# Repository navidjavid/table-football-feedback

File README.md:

# Table Football Feedback System ⚽

A smart foosball table built for the UbiLab university course. The table
identifies players by RFID, tracks the ball and score in real time, shows
match status on an on-cabinet LCD per side, and streams everything live
to a web dashboard hosted on a Raspberry Pi 4 — no internet connection
required, the Pi runs its own WiFi hotspot.

This repo contains **two independently-runnable projects**:

| Part | Where | Runs on | Language |
|---|---|---|---|
| Embedded firmware | `src/`, `include/`, `lib/` | Raspberry Pi Pico 2 W ×2 | C (Pico SDK) |
| Server + dashboard | `server/` | Raspberry Pi 4 | Python (Flask) |

They talk to each other over MQTT/WiFi — but the two Picos also talk
**directly to each other** over a shared I2C bus, so registration keeps
working even with no Pi/WiFi present at all (see §3).

---

## 1. System overview

```
 ┌──────────────┐                 ┌──────────────────────┐   ┌──────────────────────┐
 │ Ball tracker │────I2C (shared)▶│  Side A PCB           │   │  Side B PCB           │
 │ (external,   │────────────────▶│  Pico 2W + RFID +     │◀─▶│  Pico 2W + RFID +     │
 │  other team) │  both boards    │  display (PRIMARY)    │I2C│  display (SECONDARY)  │
 └──────────────┘  listen         └───────────┬──────────┘   └──────────┬────────────┘
                                               │ MQTT/WiFi                │ MQTT/WiFi
                                               ▼                          ▼
                                   ┌─────────────────────────────────────────────┐
                                   │              Raspberry Pi 4                  │
                                   │  WiFi hotspot "TableFootball"                │
                                   │  Mosquitto MQTT broker                       │
                                   │  Flask web app (SSE) + SQLite (WAL)          │
                                   └───────────────────┬───────────────────────────┘
                                                       │ HTTP / SSE
                                                       ▼
                                           Any phone/laptop on the hotspot —
                                           live dashboard, player profiles,
                                           admin panel, tournament brackets
```

**Two independent PCBs, one per side** — each has its own Pico 2 W, PN532
RFID reader, and EA DOGL128 display. Both boards listen to the same
shared I2C bus from the ball-tracker hardware. Exactly one board is
configured `PICO_ROLE_PRIMARY` (owns reporting ball position/score/state
to the Pi); the other only reports its own side's RFID taps + heartbeat —
this avoids the server ever getting duplicate/racing data from both
boards for the same table.

**Data flow, end to end:**

1. A player taps an RFID card on either side's own PN532 reader.
2. That board reads the UID over SPI, registers it locally (own side's
   roster, up to 2 players for 2v2), and:
   - broadcasts it directly to the **sibling board** over the shared I2C
     bus (a board briefly becomes I2C master to send this — see §3),
     so the other side learns about it **with no Pi/WiFi involved**;
   - publishes it to the Pi over MQTT, which is authoritative for
     identity/history — it resolves the UID against its own SQLite
     database (or creates a guest), decides when the match should
     start, and echoes the resolved name back.
3. The primary board republishes ball x/y/speed/score at ~12 Hz from the
   shared I2C feed; the dashboard renders this as a moving dot on a mini
   pitch.
4. Goals are detected locally (baseline-diffed against the ball
   tracker's own score fields, not trusted directly) on **both** boards
   independently, each updating its own display; the primary board's
   published state drives the dashboard's "GOAL!" animation.
5. At game end, the Pi saves the full match (mode, score, players,
   fastest shot, winner) to SQLite — shows up in player profiles, match
   history, and tournament brackets.
6. If a table gets stuck in `GAME_PLAYING` with no update for 45s (a
   board crashed/rebooted mid-match), the Pi's own watchdog auto-abandons
   it — so a later reconnect never resumes a long-dead game.

`[PICTURE: photo of the assembled table — both enclosures, PN532s, LCDs visible]`

---

## 2. Physical components & wiring

### Hardware list (×2, one set per side)

- **Raspberry Pi Pico 2 W** — WiFi, RFID, display, local game logic
- **PN532 NFC/RFID reader module**, configured in **SPI mode** (DIP
  switches: SEL0=OFF, SEL1=ON)
- **EA DOGL128L-6** graphic LCD, 128×64, reflective (no backlight),
  driven with **bit-banged SPI** (hardware SPI caused timing issues on
  this clone)
- A custom 3D-printed enclosure (front panel + back shell,
  `hardware/enclosure/` in a sibling directory to this repo — not
  version-controlled here) with a display window and a cable
  pass-through for the shared I2C bus
- RFID cards, one per player — UID is the player's identity end to end

Plus shared infrastructure:
- An external **ball-tracker** (built by another team) that writes ball
  position packets over I2C to both boards
- **Raspberry Pi 4** (any RAM tier) + microSD (16 GB+) + 5V/3A USB-C
  power supply — runs the WiFi hotspot, MQTT broker, and Flask server

`[PICTURE: each component individually — Pico board, PN532 module with DIP switches labeled, EA DOGL128 display, an assembled enclosure, an RFID card]`

### Real-world table dimensions

The physical table is **140 cm long × 76 cm wide**. The dashboard's
field visualization is intentionally drawn at this exact 140:76 aspect
ratio (`server/static/style.css`, `.field { aspect-ratio: 140 / 76; }`),
and ball coordinates are normalized to a 0–1000 × 0–500 grid before
being sent over MQTT so the same ratio holds end to end.

`[PICTURE: top-down schematic of the table with dimensions labeled, goal positions marked]`

### Pin connections — per side board

| Component | Signal | Pico GPIO | Physical pin |
|---|---|---|---|
| PN532 (SPI1) | SCK | GP10 | 14 |
| | MOSI | GP11 | 15 |
| | MISO | GP12 | 16 |
| | NSS/CS | GP13 | 17 |
| | RSTO | GP15 | 20 |
| | VCC / GND | 3.3V / GND | 36 / 38 |
| EA DOGL128 (bit-bang SPI) | SI (MOSI) | GP19 | 25 |
| | SCL (SCK) | GP18 | 24 |
| | A0 (data/cmd) | GP20 | 26 |
| | RST | GP21 | 27 |
| | CS1B | GP17 | 22 |
| Shared ball-tracker I2C bus | SDA | GP4 | 6 |
| | SCL | GP5 | 7 |

The display additionally needs **9 capacitors** for its internal charge
pump (5×1µF on V0–V4, 3×1µF on the CAP1/2/3 chain, 4.7µF on VOUT) — see
[`docs/hardware_connections.md`](docs/hardware_connections.md) for the
full, datasheet-verified capacitor wiring table; it will not power on
without them, and the topology is easy to get wrong (this project did,
once, before it was corrected).

The shared I2C bus needs **4.7kΩ pull-ups** on both SDA and SCL, and all
boards (both side PCBs + the ball tracker) must share a common GND.

`[PICTURE: wiring diagram / breadboard schematic showing all of the above]`

### PCB layout (KiCad)

The per-side board above is laid out in KiCad as
[`PCB/ubi_lab.kicad_sch`](PCB/ubi_lab.kicad_sch) +
[`PCB/ubi_lab.kicad_pcb`](PCB/ubi_lab.kicad_pcb) — open both together in
**KiCad 10**. It's a two-layer, 1.6 mm board with a **76 × 68 mm** outline,
carrying a socket footprint for a Pico-family board on the back plus three
connectors: `J1` (8-pin, PN532, fed from the board's 3.3V rail), `J2`
(40-pin, EA DOGL128L-6), and `J3` (4-pin, labeled `I2C_SIMULATOR` — VBUS/
GND/SDA/SCL on pins 1–4, for bench-testing against `test_i2c_simulator`
before the real ball tracker is wired in). `R1`/`R2` are the 4.7kΩ I2C
pull-ups called out above.

A few things to confirm before sending a board to fab or assembling one:

- The custom `ubi_lab:RaspberryPi_Pico_Socket_THT` footprint is embedded
  in the PCB, but its source library isn't in this repo — KiCad will need
  it to re-sync the PCB from schematic edits.
- The symbol/footprint say `RaspberryPi_Pico_W`, and the socket
  footprint's own description also mentions Pico 2 W — double check the
  exact variant, header orientation, and display-module/connector mating
  against the physical parts on hand.
- Schematic and PCB disagree on some capacitor reference designators
  (e.g. a PCB ref like `1µF7` vs. the schematic's `C` prefix) — run
  KiCad's ERC/DRC and reconcile annotations before fabrication.

### Software-side bus configuration

| Parameter | Value |
|---|---|
| SPI1 (PN532) speed | 1 MHz |
| I2C0 speed | 9600 baud |
| I2C slave address | `0x42` (shared by both side boards — see §3) |
| Display contrast | `0x13` |

Full pinout reference: [`docs/hardware_connections.md`](docs/hardware_connections.md).

---

## 3. Embedded firmware (Raspberry Pi Pico)

Built with the **Pico SDK 2.2.0**, targeting `pico2_w`, using **lwIP in
polling mode** (`NO_SYS=1` — no RTOS, everything runs from one
`while(true)` loop with `cyw43_arch_poll()` keeping WiFi/MQTT alive).

The **same firmware image** runs on both side boards — which side/role a
board plays is a compile-time config block at the top of `src/main.c`:

```c
#define MY_SIDE            'A'   // 'A' on this board, 'B' on the other
#define PICO_ROLE_PRIMARY  1     // 1 on exactly ONE board
#define PICO_ID    "pico-side-a" // must be unique per board
```

Flip these three, rebuild, and flash the other board.

### Source layout

| File | Responsibility |
|---|---|
| `src/main.c` | WiFi connect (with on-screen boot status), MQTT init, main loop |
| `src/rfid_handler.c` + `lib/pn532/pn532.c` | PN532 SPI driver + tap-debounce state machine |
| `src/i2c_comms.c` | Ball-position ring buffer **and** the offline peer-tap link between the two boards (see below) |
| `src/game_logic.c` | Local game state machine (`GAME_WAITING` → `GAME_PLAYING` → `GAME_OVER`), up to 2 players/side, goal detection, fastest-shot tracking |
| `src/display_manager.c` + `lib/ea_dogl128/` | Renders game state to the on-cabinet LCD |
| `src/pico_mqtt.c` + `include/pico_mqtt.h` | lwIP raw MQTT client wrapper — connects (with a Last-Will-Testament), publishes heartbeat/RFID/state/ball, subscribes to player/sync/rfid/cmd |
| `lwipopts.h` | lwIP buffer/pool sizing — tuned specifically to survive MQTT's keep-alive timers (see bug notes below) |

### Offline board-to-board link (no Pi/WiFi required)

Both boards need to know about **both** sides' registered players, but
cross-board MQTT sync only works when the Pi is reachable — and the PCBs
are already assembled with no spare wiring for a dedicated link. Instead,
the two boards share the same physical I2C bus the ball tracker uses:

- The ball tracker is the bus's only permanent master, always **writing**
  to address `0x42`; both boards listen there as slaves (a
  write-only-broadcast trick — see `include/i2c_comms.h`).
- When a card taps on one side, that board briefly becomes the I2C
  master itself (`i2c_slave_deinit()` → write → `i2c_slave_init()`,
  the Pico SDK's documented idiom for this) and writes a short 9-byte
  message to that same shared address. The sibling board, still
  listening normally, receives it — distinguished from ball-data packets
  purely by a different sync header.
- Standard I2C multi-master arbitration handles the rare case of
  colliding with the ball tracker's own write; a lost attempt is simply
  dropped (a tap is a one-off, low-frequency event, so this is an
  accepted low-stakes failure mode).

MQTT's `/rfid` topic (subscribed by both boards) is a second, best-effort
channel carrying the same information when the Pi is present — the I2C
link is what makes registration work **at all** with no Pi/WiFi.

### RFID → MQTT + I2C flow

1. `rfid_handler_scan()` polls the PN532 over SPI; a debounce window
   avoids re-firing on the same card sitting on the reader.
2. On a fresh tap, `game_lookup_player()` checks a small hardcoded
   table of known UIDs → names (demo roster: Alice, Bob, Carol, Dave)
   purely so the **local LCD** can show a name immediately.
3. The tap is registered locally (own side, next open slot), broadcast
   to the sibling board over I2C, and published to
   `tablefootball/table/<id>/rfid`. The Pi is the identity authority —
   it resolves the UID against its own SQLite `players` table and
   echoes the resolved name + slot back over
   `tablefootball/pico/<id>/player`.

### Ball tracking → MQTT flow

The ball tracker writes a 20-byte binary packet over I2C
(`SYNC_A SYNC_B x y prev_x prev_y field_w field_h speed possession
score_a score_b`, see `include/i2c_comms.h`). `i2c_comms_poll()` drains
this from a ring buffer filled by an I2C-slave interrupt handler — the
same ring buffer also carries the peer-tap messages above, distinguished
by sync header. `game_update()` diffs the embedded score against its
last-seen baseline to detect goals (rather than trusting the raw score
directly), and the ball position is rescaled to a 0–1000×0–500 grid
before the **primary** board publishes it on
`tablefootball/table/<id>/ball` at roughly 12 Hz.

`[PICTURE: serial console screenshot showing RFID tap + MQTT publish logs]`

### MQTT topics

**Published by each Pico:**

| Topic | Rate | Payload |
|---|---|---|
| `tablefootball/pico/<id>/heartbeat` | every 5s | online status, IP, firmware version, uptime |
| `tablefootball/table/<id>/rfid` | on tap | UID, side, slot |
| `tablefootball/table/<id>/state` | ~1/s, primary only | score, mode, fastest shot, winner (on GAME_OVER) |
| `tablefootball/table/<id>/ball` | ~12 Hz, primary only | x, y, speed |
| `tablefootball/pico/<id>/status` | LWT | `online:false`, set on disconnect |

**Subscribed by each Pico** (the Pi is source of truth for identity/state,
but the board must never depend on it being reachable — see §"Offline
board-to-board link" above):

| Topic | Purpose |
|---|---|
| `tablefootball/pico/<id>/player` | Authoritative name for a resolved tap |
| `tablefootball/table/<id>/sync` | Full roster + score/state snapshot (retained) — reconciles admin-driven registration changes, which produce no RFID tap at all |
| `tablefootball/table/<id>/rfid` | The sibling board's own taps (same topic it publishes to) |
| `tablefootball/pico/<id>/cmd` | Admin-panel commands: identify / reset_match / clear_players / show_message |

### Bugs worth knowing about (and their fixes)

These came up while building this firmware and are good examples of how
easy it is to silently break shared resources or drop a field across a
protocol boundary:

1. **I2C bytes dropped during every RFID scan.** `rfid_handler.c`
   disables `I2C0_IRQ` for the duration of `pn532_read_card()` to keep
   the I2C slave handler from interfering with SPI timing. But PN532's
   internal "wait for ready" polling loop can run for up to ~250ms per
   scan, and the IRQ stayed off that whole time — so every ball-position
   byte arriving during a card scan was lost. **Fix:** the wait loop now
   masks `I2C0_IRQ` only for the few microseconds of the actual SPI
   status read, unmasked during each 1ms sleep in between.
2. **`*** PANIC *** sys_timeout` crash.** lwIP's default
   `MEMP_NUM_SYS_TIMEOUT` pool wasn't enough once MQTT's keep-alive timer
   joined it. **Fix:** `lwipopts.h` explicitly sets it to 16.
3. **Admin dashboard commands did nothing on real hardware.** The server
   published to `tablefootball/pico/<id>/cmd` from the start, but the
   firmware never subscribed to that topic at all — every "Identify" /
   "Reset Match" / "Message" button silently no-op'd. Fixed by actually
   subscribing and dispatching (see `on_pi_cmd()` in `main.c`).
4. **A 2v2 name-correction bug.** The Pi's per-tap name resolution always
   corrected roster slot 1, no matter which slot the response was
   actually about — invisible in 1v1 (only one slot exists), but
   resolving a *second* player's name would silently overwrite the
   first player's name too. Fixed by having the server include (and the
   firmware use) the actual slot number in that message.
5. **A NULL-pointer crash with no Pi present.** If the Pi's hotspot
   simply doesn't exist at boot, `mqtt_app_init()` is never called, so
   the internal MQTT client stays `NULL` — but every heartbeat/RFID
   publish still tried to reconnect through it, crashing on first use.
   Fixed with a guard so every publish path is a safe no-op with no
   client. This is exactly the "must work fully offline" requirement,
   caught by testing the actual no-Pi scenario rather than just a
   dropped-connection one.

### Building & flashing

```bash
# Requires the Pico SDK (2.2.0) + arm toolchain + CMake + Ninja.
mkdir build && cd build
cmake -G Ninja ..
ninja table-football
```

Flip `MY_SIDE`/`PICO_ROLE_PRIMARY`/`PICO_ID` at the top of `src/main.c`
(see above), rebuild, and repeat for the other side's board.

Hold **BOOTSEL**, plug the Pico in (it mounts as a USB drive), then drag
`build/table-football.uf2` onto it.

There are also standalone test targets for bringing up hardware in
isolation without the full stack — useful when debugging a single
peripheral (see `tests/`):

| Target | Tests |
|---|---|
| `test_i2c_simulator` | Fakes ball movement over I2C — a second Pico can stand in for the real ball tracker |
| `test_pn532` | Raw PN532 SPI bring-up (firmware version + card polling), independent of the rest of the stack |
| `test_pn532_lib` | Same, using the actual `lib/pn532/pn532.c` driver the main firmware uses |
| `test_i2c_scan` | Protocol-independent I2C bus scanner (bypasses custom SPI/I2C code entirely — useful for "is this chip even alive" questions) |

---

## 4. Server & dashboard (Raspberry Pi 4)

Everything in `server/` — see [`server/README.md`](server/README.md)
for the full setup walkthrough, troubleshooting table, and MQTT
cheat-sheet. Summary:

### Stack

- **NetworkManager hotspot** — the Pi broadcasts its own WiFi network
  (`TableFootball`), so the whole system works with zero internet/router
  dependency.
- **Mosquitto** — local MQTT broker on port 1883.
- **Flask** (`server/app.py`) — HTTP routes, admin auth, and an
  `/events` SSE endpoint that streams `table_state`, `ball_position`,
  `player_update`, and `pico_status` events to every open browser.
- **`mqtt_client.py`** — subscribes to `tablefootball/#`, owns the
  authoritative game state machine per table:
  `WAITING → PLAYERS_REGISTERING → GAME_PLAYING → GAME_OVER / ABANDONED`,
  and writes everything through to SQLite.
- **SQLite (WAL mode)** — `players`, `live_tables`, `live_players`,
  `matches`, `match_players`, `pico_devices`, `tournaments` /
  `tournament_entries` / `tournament_matches`.
- **A watchdog thread** — marks a Pico offline after 30s of silent
  heartbeat, and (separately) auto-abandons a table stuck in
  `GAME_PLAYING` with no `/state` update for 45s, so a board that
  crashed mid-match doesn't leave a permanently "live" game behind.

### Dashboard (`server/static/script.js`, `templates/index.html`)

- One page, no install — any device on the hotspot opens
  `http://tb.local`.
- Real-time via SSE, with an automatic 5-second polling fallback if the
  stream drops.
- Each table card shows: player name(s) per side (colored pill, with a
  Guest/Registered badge, up to 2 names per side for 2v2), live score in
  large digits, a mini pitch drawn at the table's real 140:76 ratio with
  goal markers at each end and a live ball dot, best-shot speed, and a
  winner/abandoned banner.
- **Goal celebration:** when a side's score increases, a 2-second
  animated "GOAL!" banner pops over the pitch, colored and named for
  the scoring side.
- Clicking a row in the players table opens that player's full profile
  page (`/player/<uid>`) — match history and a fastest-shot-over-time
  chart.

`[PICTURE: screenshot of the dashboard mid-match, ideally caught mid-goal-animation]`

### Player profiles, admin & tournaments

- `/player/<uid>` — games/wins/losses, best shot, full match history,
  and (browser permitting) a fastest-shot-over-time chart.
- `/admin` — rename guest players into registered ones, watch Pico
  online/offline status, per-Pico commands (identify/reset/clear/message —
  see §3), and a tournament manager: create a bracket, add entries,
  auto-generate a single-elimination tree (byes go to the top seeds,
  never bye-vs-bye), assign a pending match to a live table, and watch
  it auto-advance as matches finish. Basic auth via `.env`'s
  `ADMIN_PASSWORD`.

`[PICTURE: screenshot of a player profile page, the admin panel, and a tournament bracket]`

### Try it without real Picos

```bash
cd server
python tests/simulate_game.py          # full match: heartbeat → register → goals → GAME_OVER
python tests/simulate_rfid.py DBEF7005 A
```

---

## 5. Known limitations / next steps

- **Offline match history sync** — a match played entirely while a Pico
  is disconnected from the Pi never reaches match history/stats once it
  reconnects (registration itself works fully offline via the I2C peer
  link in §3; only the *server-side record* of that match is missing).
- **Local "tap out" while offline** — tapping an already-seated card is
  meant to deregister that player (the server already treats a repeat
  tap this way); the local firmware currently just ignores a repeat tap
  as a duplicate, so leaving mid-game only works once the Pi is
  reachable to correct it via `sync`.
- **Self-service player registration** — a truly unknown card currently
  becomes a "Guest" automatically; naming a guest still requires the
  admin panel rather than a prompt on the dashboard itself.
- **Real ball tracking** — the ball-tracker hardware is owned by another
  team; this repo only defines the I2C packet format it must produce.
- **HTTPS / session expiry** — fine on a closed local hotspot, but would
  need hardening before exposing the admin panel beyond the LAN.

`[PICTURE: optional roadmap graphic]`

---

## Repository layout

```
table-football/
├── src/                  Pico firmware: main.c, rfid_handler.c, i2c_comms.c,
│                         game_logic.c, display_manager.c, pico_mqtt.c
├── include/              Public headers for the above
├── lib/
│   ├── pn532/            PN532 SPI driver
│   └── ea_dogl128/       EA DOGL128 display driver
├── tests/                Standalone Pico test harnesses (see §3 table)
├── PCB/                  KiCad schematic + PCB for the per-side controller board (see §2)
├── docs/
│   ├── hardware_connections.md   Full pinout + capacitor wiring reference
│   └── hardware_setup.md
├── lwipopts.h            lwIP buffer/pool sizing (tuned for MQTT keep-alive)
├── CMakeLists.txt        Builds table-football + all standalone test targets
└── server/               Flask + MQTT + SQLite server and dashboard
    ├── app.py, mqtt_client.py, database.py, state.py, config.py
    ├── templates/, static/        Dashboard, player profile, admin UI
    ├── tests/                     MQTT simulators (run the server without real Picos)
    ├── scripts/                   setup_hotspot.sh, backup_db.sh
    └── systemd/                   football.service for boot-time autostart
```

The 3D-printable enclosure design (`enclosure.scad` + exported STLs)
lives in a sibling `hardware/enclosure/` directory outside this repo,
not version-controlled here.

## Prerequisites

- [Pico SDK](https://github.com/raspberrypi/pico-sdk) 2.2.0 + arm-none-eabi
  toolchain + CMake + Ninja, for the firmware.
- Python 3.11+ and Mosquitto, for the server (see
  [`server/README.md`](server/README.md) for the full Raspberry Pi setup).

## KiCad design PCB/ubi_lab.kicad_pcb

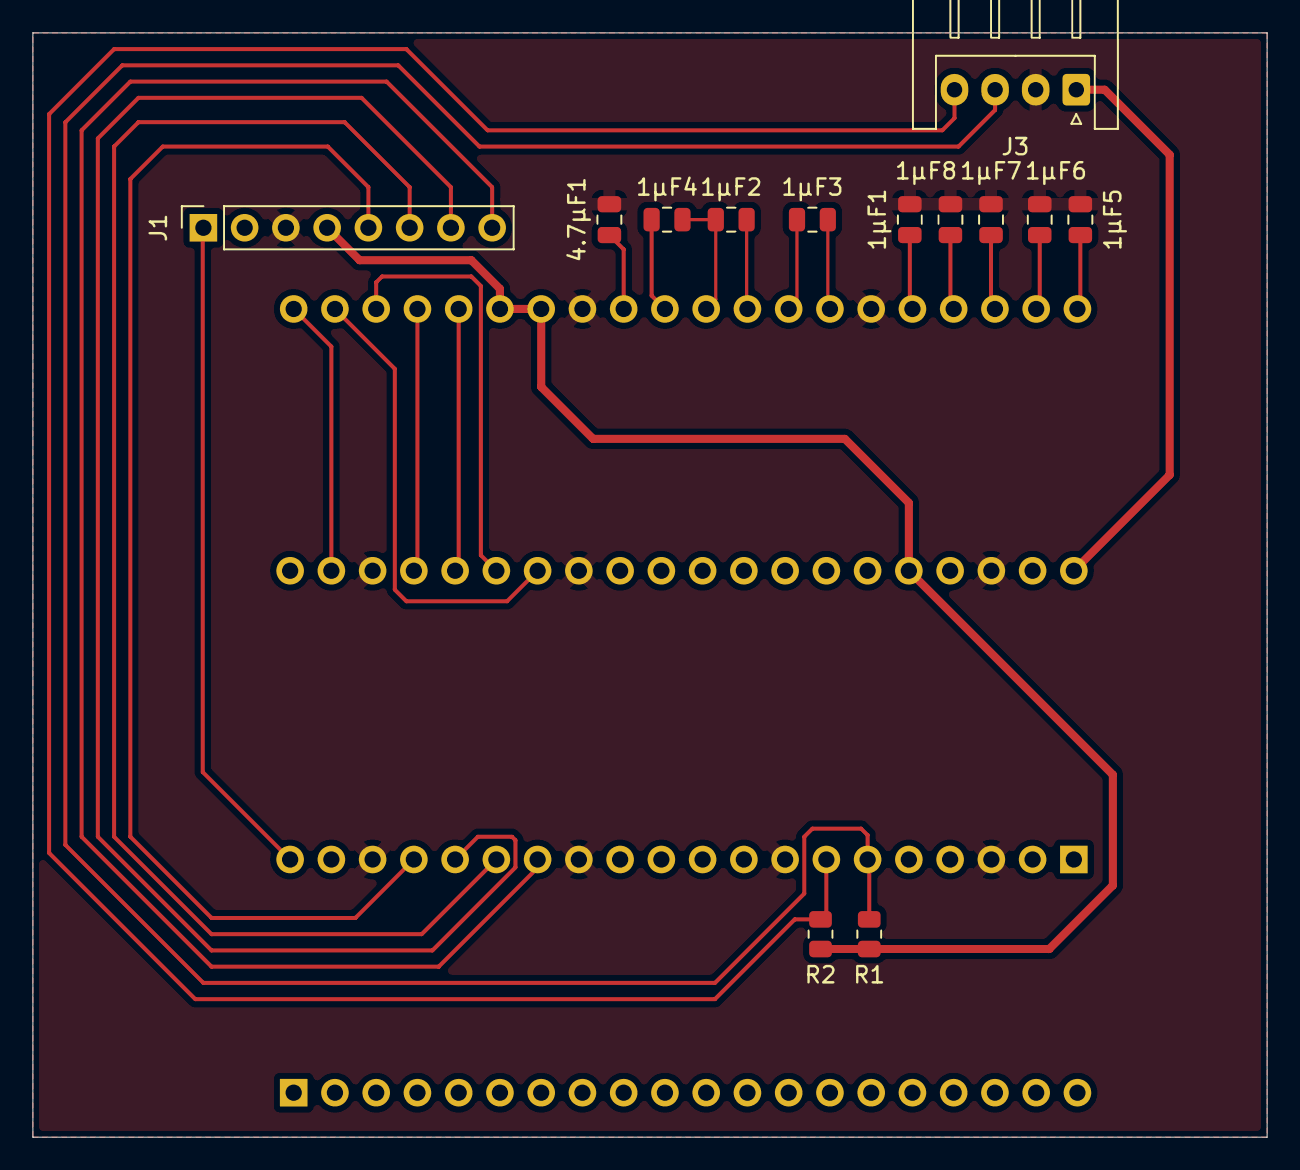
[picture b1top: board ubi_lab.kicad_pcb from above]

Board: 2 copper layers, 76.0 x 68.0 mm, 15 parts (1 on the bottom side), 26 nets.

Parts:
1µF1, 1µF2, 1µF3, 1µF4, 1µF5, 1µF6, 1µF7, 1µF8: 1µF; C_0805_2012Metric
4.7µF1: 4.7µF; C_0805_2012Metric
J1: PN532; PinSocket_1x08_P2.54mm_Vertical
J2: EA_DOGL128L_6; EA_DOGL128-6
J3: I2C_SIMULATOR; JST_XH_S4B-XH-A_1x04_P2.50mm_Horizontal
R1, R2: 4.7k; R_0805_2012Metric
U1: RaspberryPi_Pico_W; RaspberryPi_Pico_Socket_THT

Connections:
+3V3: J1.4, J2.34, J2.35, R1.1, R2.1, U1.36 (3V3)
/LCD_A0: J2.38, U1.26 (GPIO20)
/LCD_CAP1N: 1µF2.2, 1µF4.2, J2.30
/LCD_CAP1P: 1µF2.1, J2.29
/LCD_CAP2N: 1µF3.2, J2.27
/LCD_CAP2P: 1µF3.1, J2.28
/LCD_CAP3P: 1µF4.1, J2.31
/LCD_CS: J2.40, U1.22 (GPIO17)
/LCD_MOSI: J2.36, U1.25 (GPIO19)
/LCD_RST: J2.39, U1.27 (GPIO21)
/LCD_SCK: J2.37, U1.24 (GPIO18)
/LCD_V0: 1µF5.1, J2.21
/LCD_V1: 1µF6.1, J2.22
/LCD_V2: 1µF7.1, J2.23
/LCD_V3: 1µF8.1, J2.24
/LCD_V4: 1µF1.1, J2.25
/LCD_VOUT: 4.7µF1.1, J2.32
/RFID_CS: J1.5, U1.17 (GPIO13)
/RFID_MISO: J1.7, U1.16 (GPIO12)
/RFID_MOSI: J1.6, U1.15 (GPIO11)
/RFID_RST: J1.1, U1.20 (GPIO15)
/RFID_SCK: J1.8, U1.14 (GPIO10)
/SCL: J3.4, R2.2, U1.7 (GPIO5)
/SDA: J3.3, R1.2, U1.6 (GPIO4)
GND: 1µF1.2, 1µF5.2, 1µF6.2, 1µF7.2, 1µF8.2, 4.7µF1.2, J1.3, J2.26, J2.33, J3.2, U1.3 (GND), U1.8 (GND), U1.13 (GND), U1.18 (GND), U1.23 (GND), U1.28 (GND), U1.38 (GND)
VBUS: J3.1, U1.40 (VBUS)

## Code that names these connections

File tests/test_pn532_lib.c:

// Standalone test using the ACTUAL production driver (lib/pn532/pn532.c),
// the one that reportedly worked on breadboard last month — not a
// rewritten/experimental version. Same pins and config as rfid_handler.c.

#include <stdio.h>
#include "pico/stdlib.h"
#include "hardware/spi.h"
#include "pn532.h"

#define RFID_SCK  10
#define RFID_MOSI 11
#define RFID_MISO 12
#define RFID_CS   13
#define RFID_RST  15

int main(void) {
    stdio_init_all();
    sleep_ms(2000);

    printf("\n========================================\n");
    printf("PN532 LIBRARY TEST (lib/pn532/pn532.c, production driver)\n");
    printf("========================================\n");
    printf("SPI1  SCK=GP%d  MOSI=GP%d  MISO=GP%d  CS=GP%d  RST=GP%d\n",
           RFID_SCK, RFID_MOSI, RFID_MISO, RFID_CS, RFID_RST);

    PN532Config cfg = {
        .spi = spi1, .pin_sck = RFID_SCK, .pin_mosi = RFID_MOSI,
        .pin_miso = RFID_MISO, .pin_cs = RFID_CS, .pin_rst = RFID_RST,
    };
    pn532_init(&cfg); // prints its own diagnostics (see pn532.c)

    printf("\nPlace an NFC/RFID card on the reader.\n");

    uint8_t uid[4];
    while (true) {
        int status = pn532_read_card(uid);
        if (status == PN532_OK) {
            printf("[CARD] UID=%02X:%02X:%02X:%02X\n", uid[0], uid[1], uid[2], uid[3]);
            pn532_halt();
            sleep_ms(1000);
        }
        sleep_ms(200);
    }
    return 0;
}

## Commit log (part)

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2026-06-02 add RFID library
2026-06-08 fix bugs and add a demo
2026-06-10 Add PN532 RFID driver and hardware connection documentation
    - Implemented PN532 driver in C for Raspberry Pi Pico with SPI interface.
    - Added hardware connection documentation for the Table Football Feedback System, detailing connections for PN532 RFID Reader and EA DOGL128L-6 Display.
    - Created test application for PN532 to verify functionality and read card UID.
    - Established I2C communication setup between main and simulator Pico boards.
    - Included power rail summary and software configuration parameters in documentation.
2026-06-16 Refactor project structure and add lwIP configuration for networking
2026-06-21 Create README.md for Server
2026-06-21 Create implementation_prompt - temporary
2026-06-22 Add dark theme styles, systemd service, and admin panel
    - Created a new CSS file for dark theme styles to enhance readability.
    - Added systemd service file for running the Flask server under the `pi` user, ensuring it starts after the MQTT broker.
    - Included README for systemd setup instructions.
    - Developed admin panel HTML template for managing Pico devices and players.
    - Implemented admin login page for secure access to the admin panel.
    - Updated main index page to include links to the admin panel and display live tables and player stats.
2026-06-24 Add MQTT client implementation for Pico
    - Introduced `pico_mqtt.h` and `pico_mqtt.c` to provide a thin wrapper around lwIP's MQTT client.
    - Implemented functions to initialize the MQTT client, check connection status, and publish various message types:
    - Heartbeat messages
    - RFID events
    - Game state updates
    - Ball position updates
2026-06-24 update read me
